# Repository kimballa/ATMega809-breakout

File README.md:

# ATMega809 breakout board

PCB design for Atmel AVR ATMega809 breakout board. Capabilities compatible
with Arduino Nano Every (ATMega4809) and all other `ATMega{8/16/32/48}09`
and `x19` MCUs.

This provides more breakout pins from the 48-pin TQFP MCU than Nano Every
or other Arduinos.

## Power

Power can be supplied in 3 ways:

* The USB port `VUSB` is directly passed (unregulated) to the MCU
* Power on `VIN` will power a regulator that can operate at 5V0 or 3V3.
* Directly provide power to the `VDD` pin (unregulated)

### Caution!

Do not provide power to the regulator through `VIN` at the same time as
providing USB power through `VUSB`.

There are protection diodes so it should not immediately fail, but there is no
regulator shut-off circuit that detects USB power, so there may be unanticipated
consequences, especially if you plug in the USB power while the device is turned
on already by VIN.

This is especially true if the regulator is configured for 3V3, as the MCU will
immediately see its supply voltage increase while running.

`VDD` is also exposed on pin 15. You can use this to source power from the
linear regulator or to sink power back to the MCU. There is no diode or polyfuse
on this (or any) power bus of the device. Do not drive power into the device
through this pin at the same time as the regulator is powered.

### Configurable Regulator

The device is powered through an NCP1117LP adjustable 1A linear regulator.

This is configured for 5V0 operation by default. Closing the `3V3_SEL` jumper will
reconfigure it for 3V3. A task best performed with the device unpowered.

* If powering the device for 5V0, you must supply 6.5V or greater on `VIN`
* If powering the device for 3V3, you must supply 5.0V or greater on `VIN`
* `VIN` absolute maximum rating is 16V. For safe thermal operation, target
  `VDD + 3V` or less.

### Power limits and thermal capacity

You can draw power from the regulator's output `VDD` on pin 15. The total
power available (including MCU power budget) is 1A.

The ATMega809 can drive up to 15mA per pin in 5V0 mode, and 7.5mA in 3V3.
Absolute maximum rated drive per pin is +/-40mA. MCU absolute maximum VDD pin
input is 200mA.

The main limit to current is based on the LDO's thermal regulation capability.
LDO power dissipation in this implementation has an absolute maximum 825 mW. LDO
power dissipated is given by `(VIN - VDD - 0.35V)(IDD)`. Keeping `VIN` as close
to the 6.5V or 5.0V supply requirement gives more headroom for more current.

If VDD = 5V0 and VIN = 6V5, maximum current is 715 mA.

If VDD = 3V3 and VIN = 5V0, maximum current is 610 mA.

## Clock speed configuration

The MCU boots with `CLK_MAIN` driven by the `OSC20M` oscillator which is in
either 20MHz or 16MHz mode (check `OSCFUSE` bits to see how it is programmed),
with a `CLKDIV` of 6.

During boot, Arduino will disable the CLKDIV so your sketch is running at
the full 20 or 16MHz.

If operating in low-voltage 3V3 mode, the maximum safe clock speed is 10MHz.  So
a `CLKDIV` of at least 2 must be applied. If using an Arduino sketch on an
Arduino core compiled with default settings, the Arduino `init()` function will
fully unleash the clock divider for at least a short time before your `setup()`
method has time to pull it back to a divider of 2, which may cause boot
instability. Compiling the core with `-DFCPU=10000000` will tell Arduino to
unthrottle the clock only as far as a divider of 2.

## Level-shifting I2C Bus

The breakout board offers I2C on the `SDA`/`SCL` pins. A dual-transistor buffer
isolates the pull-up voltages seen on these pins from those seen by the MCU.
That is, a 3V3 network can communicate with an MCU operating at 5V0 or vice
versa.

You must supply power to the `VBUS` pin in order to activate the buffer and
communicate over I2C. Otherwise the external I2C bus will be fully isolated from
the MCU I2C bus. If the MCU and the external circuit are operating at the same
voltage you can connect `VBUS` to `VDD`.

You must apply external pull-up resistors to `SDA` and `SCL` to use I2C.
Typical resistor value is 4K7. The bus capacitance added by the breakout
board is typically 36 pF (per [PJA3438
datasheet](https://www.panjit.com.tw/upload/datasheet/PJA3438-AU.pdf))
[plus capacitance added by header pin, flying leads, etc].

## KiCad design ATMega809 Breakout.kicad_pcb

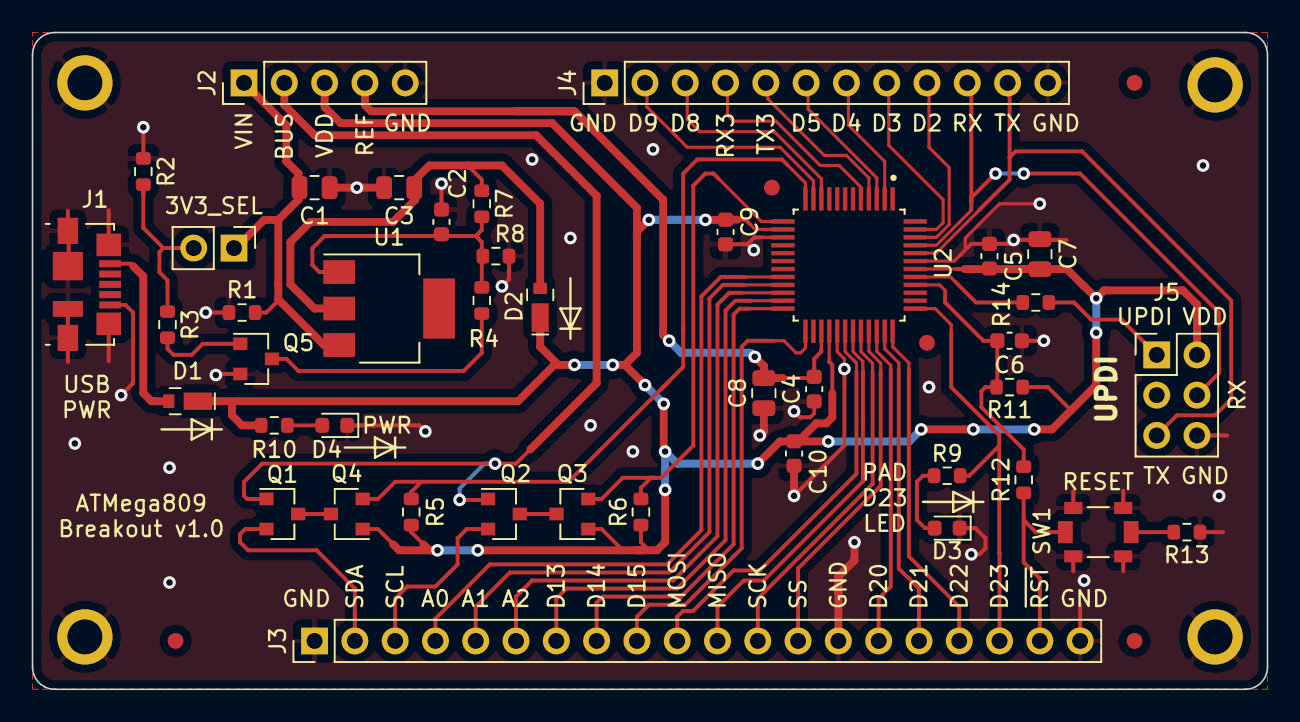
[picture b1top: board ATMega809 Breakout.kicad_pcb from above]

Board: 2 copper layers, 77.9 x 41.4 mm, 51 parts (0 on the bottom side), 48 nets.

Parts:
C1, C3, C7, C8: 10u; C_0805_2012Metric
C2, C4, C5, C6, C9, C10: 100n; C_0603_1608Metric
D1, D2: CUHS20S30; CUHS20S30_H3F
D3, D4: LTST-C193KRKT-2A; D_0603_1608Metric
FID1, FID2, FID3, FID4, FID5: Fiducial; Fiducial_1mm_Mask2mm
H1, H2, H3, H4: MountingHole_Pad; MountingHole_2.2mm_M2_ISO7380_Pad
J1: USB_B_Micro; USB_Micro-B_Molex_47346-1001
J2: Conn_01x05; PinHeader_1x05_P2.54mm_Vertical
J3: Conn_01x20; PinHeader_1x20_P2.54mm_Vertical
J4: Conn_01x12; PinHeader_1x12_P2.54mm_Vertical
J5: UPDI; PinHeader_2x03_P2.54mm_Vertical
JP1: 3V3_SEL; PinHeader_1x02_P2.54mm_Vertical
Q1, Q2, Q3, Q4, Q5: PJA3438-AU; SOT-23
R1, R2, R11: 100K; R_0603_1608Metric
R3, R12, R13: 1K0; R_0603_1608Metric
R4: 560R; R_0603_1608Metric
R5, R6: 4K7; R_0603_1608Metric
R7: 120R; R_0603_1608Metric
R8: 390R; R_0603_1608Metric
R9, R10, R14: 470R; R_0603_1608Metric
SW1: RESET; PTS820_J25K_SMTR_LFS
U1: NCP1117-ADJ_SOT223; SOT-223
U2: ATMEGA809-AF; Microchip-TQFP7x7-48

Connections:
/3V3SELECT: JP1.2, R2.2, R3.1
/A0: J3.4, U2.20
/A1: J3.5, U2.21
/A2: J3.6, U2.22
/D2: J4.9, U2.46
/D3: J4.8, U2.47
/D4: J4.7, U2.2
/D5: J4.6, U2.3
/D8: J4.3, U2.10
/D9: J4.2, U2.11
/D13: J3.7, U2.23
/D14: J3.8, U2.24
/D15: J3.9, U2.25
/D20: J3.15, U2.34
/D21: J3.16, U2.35
/D22: J3.17, U2.36
/D23: J3.18, R9.1, U2.37
/LINADJ: C2.2, R4.1, R7.2, R8.1, U1.1
/MISO: J3.11, U2.31
/MOSI: J3.10, U2.30
/RESET_MCU_L: C6.2, R11.2, R12.2, U2.40
/RX: J4.10, J5.4, U2.45
/RX3: J4.4, U2.5
/SCK: J3.12, U2.32
/SCL: J3.3, Q2.2
/SCL_MCU: Q3.2, R6.2, U2.13
/SDA: J3.2, Q1.2
/SDA_MCU: Q4.2, R5.2, U2.12
/SS: J3.13, U2.33
/TX: J4.11, J5.5, U2.44
/TX3: J4.5, U2.4
/UPDI_MCU: R14.1, U2.41
/VREF: C4.2, C8.1, J2.4, U2.27
/VREG_OUT: C3.1, D2.2, R7.1, U1.2
/VUSB: D1.2, J1.1
GND: C1.2, C2.1, C3.2, C4.1, C5.1, C6.1, C7.2, C8.2, C9.1, C10.1, D3.1, D4.1, H1.1, H2.1, H3.1, H4.1, J1.5, J1.6, J2.5, J3.1, J3.14, J3.20, J4.1, J4.12, J5.6, Q5.2, R1.1, R2.1, R8.2, R13.1, SW1.3, U2.15, U2.29, U2.43
unnamed: D3.2, R9.2
unnamed: D4.2, R10.2
unnamed: Q1.3, Q4.3
unnamed: Q2.3, Q3.3
unnamed: Q5.1, R3.2
unnamed: Q5.3, R4.2
unnamed: R13.2, SW1.2
RESET_L: J3.19, R12.1, SW1.1
UPDI: J5.1, R14.2
VBUS: J2.2, Q1.1, Q2.1
VDD: C5.2, C7.1, C9.2, C10.2, D1.1, D2.1, J2.3, J5.2, Q3.1, Q4.1, R5.1, R6.1, R10.1, R11.1, U2.14, U2.28, U2.42
VIN: C1.1, J2.1, JP1.1, R1.2, U1.3

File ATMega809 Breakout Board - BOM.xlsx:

Part no. | Reference | Value | Datasheet | Description | Manufacturer | MPN | Qty | Comment
1 | C1, C3, C7, C8 | 10u |  | 10uF 0805 X5R or X7R ceramic capacitor; 20mOhm < ESR < 10 Ohm; V_max >= 10V | Samsung Electro-Mechanics | CL21A106KOQNNNG | 4
2 | C2, C4-C6, C9, C10 | 100n | https://datasheets.kyocera-avx.com/X7RDielectric.pdf | 100nF 0603 X7R ceramic capacitor; 20mOhm < ESR < 10 Ohm | KYOCERA | 06036C104JAT2A | 6
3 | D1, D2 | CUHS20S30 | https://toshiba.semicon-storage.com/info/docget.jsp?did=6360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 | Schottky diode; V_R >= 30V; I_fwd >= 1A; 250mA < V_fwd < 340 mA @ 1A | Toshiba Semiconductor | CUHS20S30,H3F | 2
4 | D3, D4 | LTST-C193KRKT-2A | https://media.digikey.com/pdf/Data%20Sheets/Lite-On%20PDFs/L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 | Red chip LED; 0603; Vfwd = 1.8--2.0V, I_test = 2mA; >= 2mcd illumination @ 2mA | Lite-On | LTST-C193KRKT-2A | 2
5 | J1 | USB_B_Micro | https://www.molex.com/pdm_docs/sd/473461001_sd.pdf | USB Micro-B receptacle; SMT; no flanges; board-edge | Molex | 473461001 | 1
6 | J2-J4, JP1 |  | ~ | Cuttable male pin THT header strip (5, 20, 12, 2 pins), 0.1"/2.54mm pitch; 10--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 | TE Connectivity AMP Connectors | 5-146858-1 | 39 | <-- total number of header pins; but only 4 parts (header strips) to place
7 | J5 | UPDI | ~ | Male pin THT header 2-row strip (2x3 pins), 0.1"/2.54mm pitch; 10--15.0µin gold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 | Samtec | TSW-103-07-L-D | 1
8 | Q1-Q5 | PJA3438-AU | https://www.panjit.com.tw/upload/datasheet/PJA3438-AU.pdf | N-MOSFET; SOT-23; I_D >= 500mA; max V_DS >= 50V; max V_GS +/-20V; 0.4V < V_GS(t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 | Panjit Int'l. | PJA3438-AU_R1_000A1 | 5
9 | R3, R12, R13 | 1K0 | ~ | 1K0 0603 resistor; +/-1%; 1/10W | YAEGO | RC0603FR-071KL | 3
10 | R4 | 560R |  | 560R 0603 resistor; +/-1%; 1/10W | YAEGO | RC0603FR-07560RL | 1
11 | R5, R6 | 4K7 | ~ | 4K7 0603 resistor; +/-1%; 1/10W | YAEGO | RC0603FR-074K7L | 2
12 | R7 | 120R | ~ | 120R 0603 resistor; +/-1%; 1/10W | YAEGO | RC0603FR-07120RL | 1
13 | R8 | 390R | ~ | 390R 0603 resistor; +/-1%; 1/10W | YAEGO | RC0603FR-07390RL | 1
14 | R9, R10, R14 | 470R | ~ | 470R 0603 resistor; +/-1%; 1/10W | YAEGO | RC0603FR-07470RL | 3
15 | R1, R2, R11 | 100K | ~ | 100K 0603 resistor; +/-1%; 1/10W | YAEGO | RC0603FR-07100KL | 3
16 | SW1 | RESET | https://www.ckswitches.com/media/1474/pts820.pdf | Tactile momentary SPST (normally-open) switch/button; grounded. | C&K | PTS820 J25K SMTR LFS | 1
17 | U1 | NCP1117-ADJ_SOT223 | https://www.onsemi.com/pdf/datasheet/ncp1117lp-d.pdf | Adjustable linear regulator; SOT223 package; dropout voltage 1.3V @ 1A; V_in,ma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 | onsemi | NCP1117LPSTADT3G | 1
18 | U2 | ATMEGA809-AF |  | Critical component. ATMEGA809-AU also OK. -AFR and -AUR (tape & reel) packaging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 | Microchip | ATMEGA809-AF | 1

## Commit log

2022-04-20 Add README and gitignore.
2022-04-20 Initial breakout board design checkin.
    Includes circuit schematic for MCU breakout, linear regulator,
    and level-shifting I2C bus.
    Includes prototype PCB layout.
    * Everything placed. Automated DRC checks pass.
    * Seeed D4M guidelines / checklist applied.
2022-04-20 Added more README documentation.
2022-04-20 Added notes file for PCB mfr.
2022-04-21 Cleanup. Basically ready for mfg.
    * Switched USB connectors to pure-SMT assembly, no THT.
    * More trace clean-ups. Eliminated 45 deg angles in traces.
2022-04-21 Improved RESET circuitry.
    * Switch SW1 now discharges capacitor C6 to GND thru R12 (1K0) rather
    than short-circuit.
    * Added resistor R13 (1K0) between RESET_L and pull-up R11/capacitor
    C6/SW1. If an external MCU drives RESET_L low, the capacitor will
    discharge through R13 rather than short circuit, limiting max
    discharge current encountered by the GPIO to 5mA.
2022-04-21 Add resistor R14 between UPDI_MCU and UPDI pin.
    If the MCU and programmer get out of sync and each try to drive the line
    in different directions, somebody's going to have a bad time. Small
    resistor ensures device safety while allowing high-speed bandwidth.
    Value is sufficiently low that even if the programmer also has a 470R
    on the line the logic levels will still work OK.
    See discussion:
2022-04-21 Add decoupling cap C10 for AVDD pin of MCU.
    Add 100nF stabilizing ballast to AVDD input (MCU pin 28).
2022-04-21 Tweak RST protection resistor placement.
2022-04-21 Final tweaks and checks.
2022-04-22 v1.0 Release to manufacturing
    * Add BOM data to KiCAD and export to Excel.
    * Elaborate on fab notes TXT file.
    * Generate gerber files, schematic pdf, drill file, placement file for mfr.
2022-04-22 Add v1.0 pin-out pdf.
2022-04-22 Add pinout plan src excel file.
2022-05-25 Upgrade to KiCAD 6.0 format.
2022-05-27 Update pinout plan file.
    Reflect actual Arduino mapping.
2022-06-03 Update pinout to match the Arduino variant specification & add UDPI.
2022-06-03 Add pdf render of PCB layout for v1.0 run.
